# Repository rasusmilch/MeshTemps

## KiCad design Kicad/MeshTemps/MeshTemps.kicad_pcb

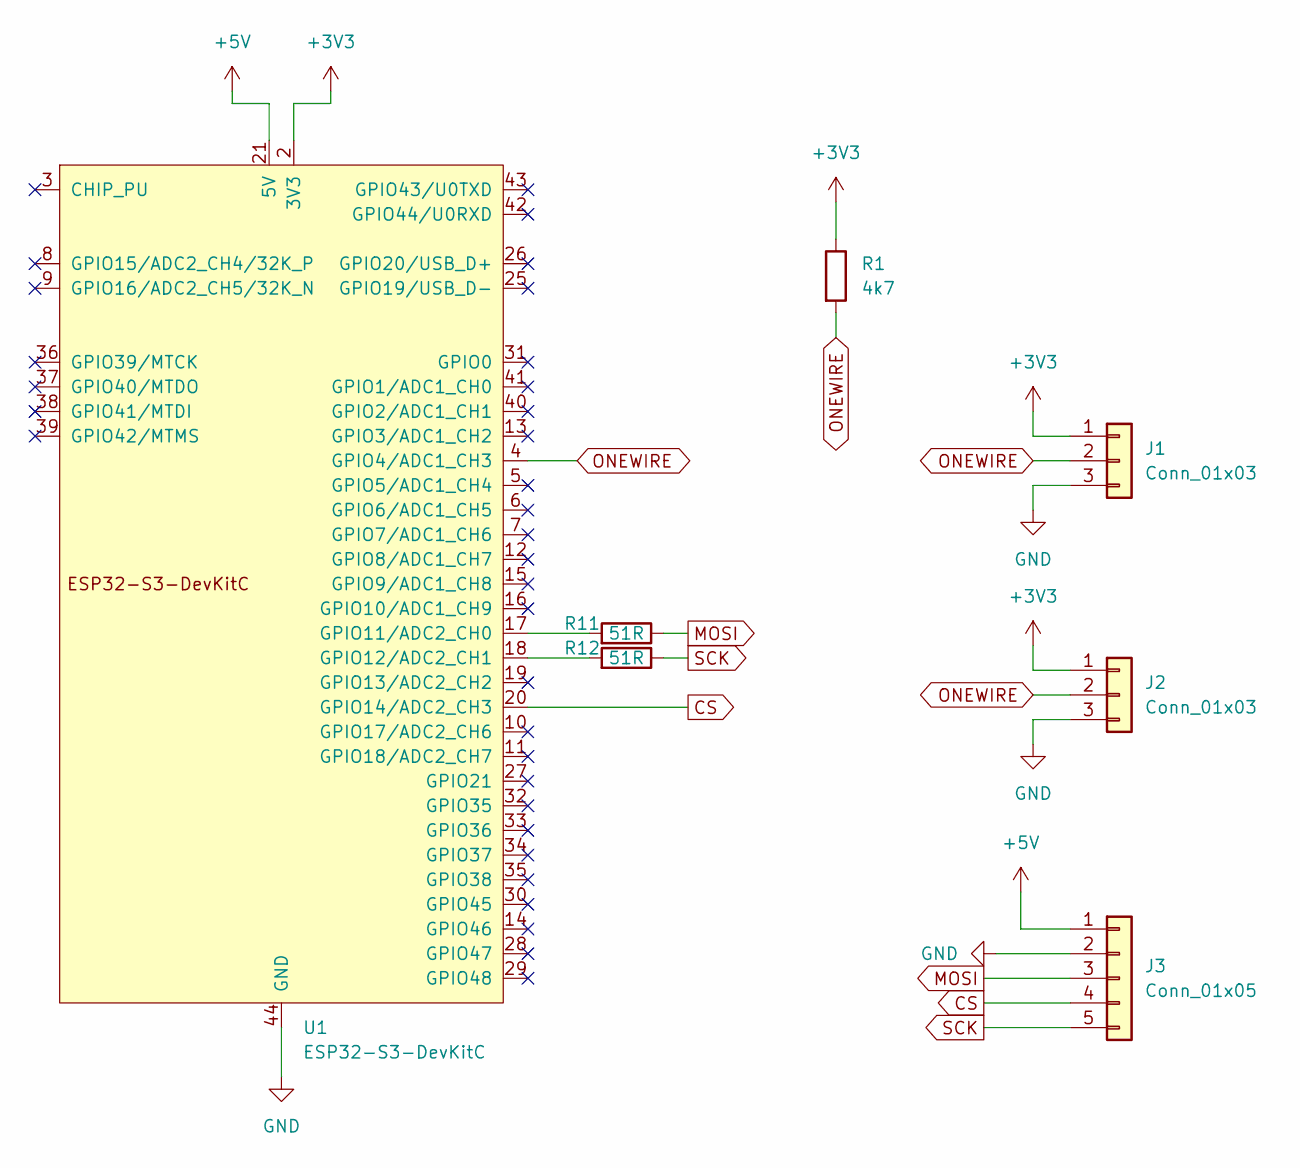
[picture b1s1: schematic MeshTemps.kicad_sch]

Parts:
J1, J2: Conn_01x03; Molex_KK-254_AE-6410-03A_1x03_P2.54mm_Vertical
J3: Conn_01x05; Molex_KK-254_AE-6410-05A_1x05_P2.54mm_Vertical
R1: 4k7; R_0603_1608Metric_Pad0.98x0.95mm_HandSolder
R11, R12: 51R; R_0603_1608Metric_Pad0.98x0.95mm_HandSolder
U1: ESP32-S3-DevKitC

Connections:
+3V3: J1.1, J2.1, R1.1, U1.1 (3V3), U1.2 (3V3)
+5V: J3.1, U1.21 (5V)
CS: J3.4, U1.20 (GPIO14/ADC2_CH3)
GND: J1.3, J2.3, J3.2, U1.22 (GND), U1.23 (GND), U1.24 (GND), U1.44 (GND)
MOSI: J3.3, R11.1
unnamed: R11.2, U1.17 (GPIO11/ADC2_CH0)
unnamed: R12.2, U1.18 (GPIO12/ADC2_CH1)
ONEWIRE: J1.2, J2.2, R1.2, U1.4 (GPIO4/ADC1_CH3)
SCK: J3.5, R12.1

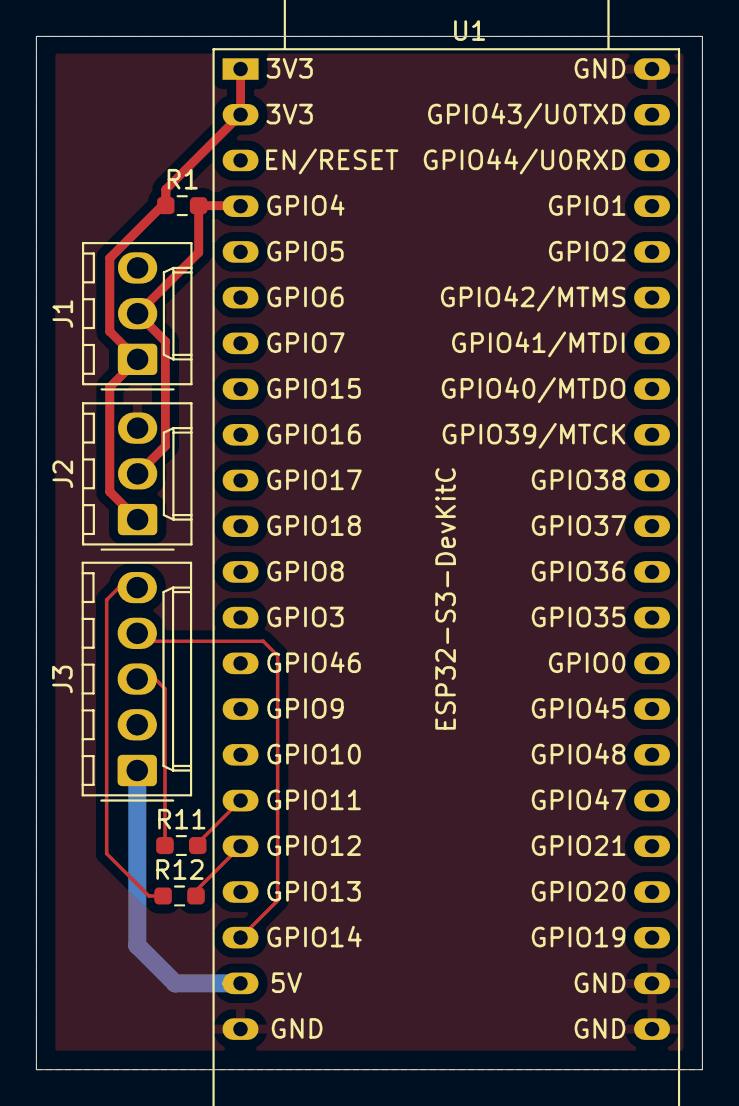
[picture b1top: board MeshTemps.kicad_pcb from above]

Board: 2 copper layers, 37.0 x 57.4 mm, 7 parts (0 on the bottom side), 9 nets.

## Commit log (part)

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2025-11-04 Trying to leverage in LVGL placeholders.
2025-11-05 Adding Waveshare screen and leaf calibration (untested)
2025-11-05 Cal and linear regression for leaf node
2025-11-06 Trying to integrate the LCD
2025-11-06 LCD initializes and draws correctly for test!
2025-11-06 Added persistant temperature display units and populates on node connection.
2025-11-06 Fixing bugs and deadlocks
2025-11-06 Fixed duplicate lines
2025-11-07 Updated to tiles, added buzzer, alert and warning limits, console commands, etc.
2025-11-07 Updated tile widgets to be persistant. Flashing tiles.
2025-11-10 Tried reverting LVGL porting config back to small interal SRAM buffer to help with pixel line drift after several hours?
2025-11-12 Added node ordering, leaf node calibrate all, naming of nodes and sensors with printable character. Need to refactor processConsole commands!
2025-11-12 Updated display to not force a refresh every minute. Also should remember all nodes seen.
2025-11-12 Separated out processconsole into serial_console with callbacks.
2025-11-13 Rewriting topology
2025-11-13 Converted to hex input and output. Topology switch on or off for excessive NVS writes. Might have fixed the constant topology writes. Topology saves with nodeID only, no more JSON.
2025-11-14 Trying to match 09_lvgl_Porting example to eliminate ghost pixels.
2025-11-15 Updating to MeshNode and MeshTile classes.
2025-11-17 Fixed labels not saving and loading properly. Removed migrating older storage versions as we prototype anyway. Added sequence numbers to leaf nodes for tracking no valid updates.
2025-11-17 Updated serial commands to include sequence number and age.
2025-11-17 Updated wrong cmddebug (should have been root not leaf.)
2025-11-18 Updated LS to iterate over MeshNodes and changed tile display to temps in the corners and larger font. Also flags and commands to make age and sensor name labels visible or invisible on the tiles.
2025-11-19 Updated GuiRebuildTiles to reorder tiles. But now we get out of memory errors?!
2025-11-19 try disable tearing mode. If still an issue, disable bounce buffer.
2025-11-20 Fixing norder and LCD buffer glitches.
2025-11-20 Updated norder. Moved more node data into MeshNode class.
2025-11-21 Fixing persistant nodes that come back. Changed background color. Fixed nodes reordering on every transmission received.
2025-11-21 Commands now print out their arguments and their actions.
2025-11-21 Collapsed flashing behavior to immediately toggle color.
2025-11-22 Fixed backgrounds not coloring, ranks not being loaded, labels not being reloaded.
2025-11-25 In progress home map
2025-11-26 Fixed house and outside container padding issues.
2025-11-26 Updated map rooms to layout. Fixed borders, tweaked house layout.
2025-11-26 Fixed dummy data to populate all various errors.
2025-11-27 Fixing leaf nodes not saving and loading calibration due to long key names.
2025-12-01 Split the root and leaf nodes into separate folders. Added NTP and wifi connection to an AP. Time is not displayed in the upper right.
2025-12-02 Fixing mesh not working and wifi does not connect to home router
2025-12-02 Adding in history to nodes and fixing wifi
2025-12-03 Fixed nodes must be on same channel as AP for NTP to work. Also, fixed some leaf node include ordering. Added ability to do hidden meshes (config time only.) Modified wifi scan command to print radio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
2025-12-03 Leaf nodes should search for mesh and change channel to match. Adding in clickable node history.
2025-12-04 Fixed leaf nodes scanning for Mesh network to choose channel. Reenabled root scan for AP. Fixed leaf node calibration not loading by switching to binary blobs.
2025-12-04 Working on leafs chasing the root. I think we need to actively ping and try all channels.
2025-12-04 Added leaf channel discovery that tries all found channels during wifi scan. Also, root heartbeat detection on leaf nodes. If a node stops seeing root announce messages it assumes the root changed ch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
2025-12-06 Fixed mesh teardown before init
2025-12-08 Updated leaf nodes to have longer timeout, and more agressive retrying. NTP now is non-blocking. Wifi connects in the background for NTP syncing. NTP pop-up should be more visible.
2025-12-09 Updated silence buzzer ability. Explored LCD panel glitches and flikery pixels.
2025-12-10 Setting up MeshNode class to store timestamps when NTP syncs and time is known for history of sensor data.
2025-12-10 Handle millis rollover when computing history epochs
2025-12-10 Store epoch timestamps inline in history samples
2025-12-12 Add serial passthrough debug mode
2025-12-12 Fixed double declaration of now_epoch and set esp-expander IO5 low to keep analog switch for CAN off (USB CDC enabled!)
2025-12-12 Fixed GUI-Node now_epoch
2025-12-12 Fixed serial_console.h include path
2025-12-12 Fixed serial include, again, and g_passthrough globals higher in the file.
2025-12-12 Clarify UART roles for GUI and bridge nodes
2025-12-12 Align bridge WiFi init with original root
2025-12-12 Align bridge mesh channel selection
2025-12-12 Restore root_announce broadcasts from bridge
2025-12-12 Add timezone controls to bridge NTP sync
2025-12-13 Apply saved mute metadata when nodes reappear
2025-12-13 Keep GUI peer count in sync
2025-12-13 Remove duplicate GUI time command
2025-12-13 Handle variable NVS lengths for buzzer settings
2025-12-13 Verify NVS ulong writes by value instead of length
2025-12-13 Verify ulong NVS writes by read-back instead of length
2025-12-13 Shorten NVS keys for buzzer settings
2025-12-13 Add ntfy notifications
2025-12-13 Centralize ntfy config on bridge
2025-12-13 Improve debug logging for bridge requests
2025-12-13 Process GUI ntfy during passthrough
2025-12-13 Improve bridge handling of GUI time requests
2025-12-13 Removed guard around SendNtfyRequestBridge
2025-12-13 Add ntfy logging on GUI and bridge
2025-12-13 Centralize bridge-GUI serial sends
2025-12-13 Clarify debug bridge logging direction
2025-12-13 Condensed debug and passthru
2025-12-13 Removed flash serial messages and fixed incorrect passthrough variable
2025-12-13 Fixed incorrect bridge RX pin definition (wire in 16, not 18, due to poor silk screening.)
2025-12-13 Handle bridge hello and wifi updates
2025-12-13 Fixed GPIO comment.
2025-12-13 Adjust node notifications
2025-12-13 Send ntfy test to both topics
2025-12-13 Emit ntfy received messages only when debug is on
2025-12-13 Fixed wrong debug variable
2025-12-13 Improve ntfy reliability between GUI and bridge
2025-12-13 Add hysteresis control for temperature limits
2025-12-14 Add serial NVS backup and restore commands
2025-12-14 Remove Wi-Fi credentials from bridge NVS dump
2025-12-14 Sort label displays for ntfy and ls
2025-12-14 Fix history view epoch reporting
2025-12-14 Changed bridge_gui baud to protect against transients.
2025-12-14 Respect units in console sensor listings
2025-12-14 Fix ntfy hysteresis thresholds
2025-12-14 Align buzzer silence with hysteresis
2025-12-14 Add map history chart overlay
2025-12-14 Guard chart tick labels against invalid buffers
2025-12-14 Minor CmdLS formatting for units.
2025-12-14 Minor formatting in CmdHist view
2025-12-14 Clamp chart tick label length
2025-12-14 Changed CmdHist number of decimal digits.
2025-12-14 Fix chart label length for UTF-8 units
2025-12-14 Fix chart tick label formatting to avoid LVGL UTF-8/float crashes
    * Write tick labels into LVGL-provided dsc->text buffer (use dsc->text_length as capacity)
    * Remove encoded-length logic / stop overwriting dsc->text_length
    * Replace float snprintf formatting with integer (0.1 unit) math for X/Y axis labels
    * Emit degree symbol as explicit UTF-8 bytes in units label
2025-12-14 Improve history chart legibility
2025-12-14 Fixing chart layout. Added MeshNode printing of history sample size for future compacting.
2025-12-14 Add I2C scan command to GUI console
2025-12-14 Fix I2C scan command compatibility
2025-12-14 Moved chart range buttons to the left. Fixed chart labels.
2025-12-14 Fixing chart banding for more visibility.
2025-12-14 Compact SensorHistorySample
2025-12-14 Trying to fix charts still
2025-12-14 Refine nvs restore raw mode handling
2025-12-14 Handle larger NVS restore JSON payloads
2025-12-14 Diagnosing NVS restore
2025-12-14 Increased buffer sizes for nvs restore.
2025-12-14 Fix NVS restore labels capacity
2025-12-14 Reboot loop
2025-12-15 Fixed NVS restore not working. Increased serial rx buffer. Implemented a raw serial aggregator. Lots of json and NVS work. Chased, found the dragon, fought it and won.
2025-12-15 Change chart scatter point size
2025-12-15 Creating historical record via FRAM and SD. In progress. Needs fleshing out.
2025-12-29 Add chart downsampling and mesh node mutex
2026-01-01 Remove chart points for cleaner look.
2026-01-02 Trying to downsample chart points, but now getting panics
2026-05-29 Add gated chart rebuild diagnostics
2026-05-29 Updates gitignore
2026-05-29 Update gitignore
2026-06-03 Fix too late RestoreLogCounters declaration
2026-06-04 Move mesh chart debug to a more accessible locatoin.
2026-06-04 Arduino setup documentation
2026-06-04 Add watchdog-safe hist fake job
2026-06-04 Fix hist fake live target selection
2026-06-04 Preserve diagnostic fake histories
2026-06-04 Hide history chart point markers
2026-06-05 Document history console commands and guard hist set
2026-06-05 Disable chart diagnostics by default
2026-06-05 Extract chart series preparation helper
2026-06-05 Fix Arduino prototype for chart series helper
2026-06-06 Add sensor history traversal helpers
2026-06-06 Added an ESP32 backtrace decode script.
2026-06-06 Starting new branch and adding PT100 Datalogger code for reference
2026-06-07 Add RAM hour history stager
2026-06-07 Clean up RAM hour stager export semantics
2026-06-07 Add SD finalized hour block writer
2026-06-07 Update anchors for heap-free SD writer gate
2026-06-07 Remove finalized hour SD full-record buffers
2026-06-07 Remove finalized hour vector helpers
2026-06-07 Remove finalized hour String path allocation
2026-06-07 Use epoch-day finalized-hour paths
2026-06-07 Clarify snapshot stack-safety guardrail
2026-06-07 Remove stale history aggregator
2026-06-07 Add finalized hour source view writer
2026-06-08 Add source status mismatch tests
2026-06-08 Add finalized hour write coalescer
2026-06-08 Update anchors for static SD buffer gate
2026-06-08 Move finalized hour SD buffers to static storage
2026-06-08 Remove legacy SdHistoryStore non-finalized APIs
2026-06-08 Add SD durability and recovery anchor
2026-06-08 Add anchor index for storage workstream
2026-06-08 Clarify anchor index durability gate precedence
2026-06-08 Add current next action anchor for storage recovery gate
2026-06-08 Include current next action anchor in index
2026-06-08 Add testing hardening anchor
2026-06-08 Add testing hardening anchor to index
2026-06-08 Add testing hardening gate to current next action anchor
2026-06-09 Add finalized-hour append file scanner
2026-06-09 Harden scanner test harness checks
2026-06-09 Add non-destructive finalized-hour recovery policy seam
2026-06-12 Update MeshTemps project intent for sensor-major SD archive
2026-06-12 Update MeshTemps roadmap for finalized-hour v2 format gate
2026-06-12 Update MeshTemps requirements for sensor-major SD archive
2026-06-12 Add MeshTemps storage decision log anchor
2026-06-12 Update v2 ABI anchor sequencing
2026-06-13 Add finalized-hour v2 format skeleton
2026-06-13 Update anchors for v2 ABI ownership rules
2026-06-14 Revise finalized-hour v2 ABI skeleton
2026-06-14 Update current next action after PR 57 validation
2026-06-14 Update MeshTemps anchors for on-disk format terminology
2026-06-14 Add pure finalized-hour v2 writer core
2026-06-14 Move v2 writer scratch into explicit workspace
2026-06-15 Harden v2 writer workspace contract tests
2026-06-15 Integrate v2 finalized hour writer in store
2026-06-15 Add SdHistoryStore v2 append tests
2026-06-15 Finalize PR 58 B2 checkpoint anchor
2026-06-16 Add finalized-hour v2 scanner core
2026-06-17 Expand finalized-hour v2 scanner coverage
2026-06-17 Add read-only v2 finalized-hour scan seam
2026-06-17 Update scanner stack anchors after validation
